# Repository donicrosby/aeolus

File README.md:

# Aeolus
A modular window extraction fan that uses common PC fans as the extraction component

## Setup
There are a few submodules that need to be pulled in this can be done by:

```bash
git clone --recurse-submodules https://github.com/donicrosby/aeolus.git
```

Or after already cloning the repo:

```bash
git clone ttps://github.com/donicrosby/aeolus.git
git submodule update --init --recursive
```

## Notes
This is a Kicad 9 project, ensure that you use that version when viewing

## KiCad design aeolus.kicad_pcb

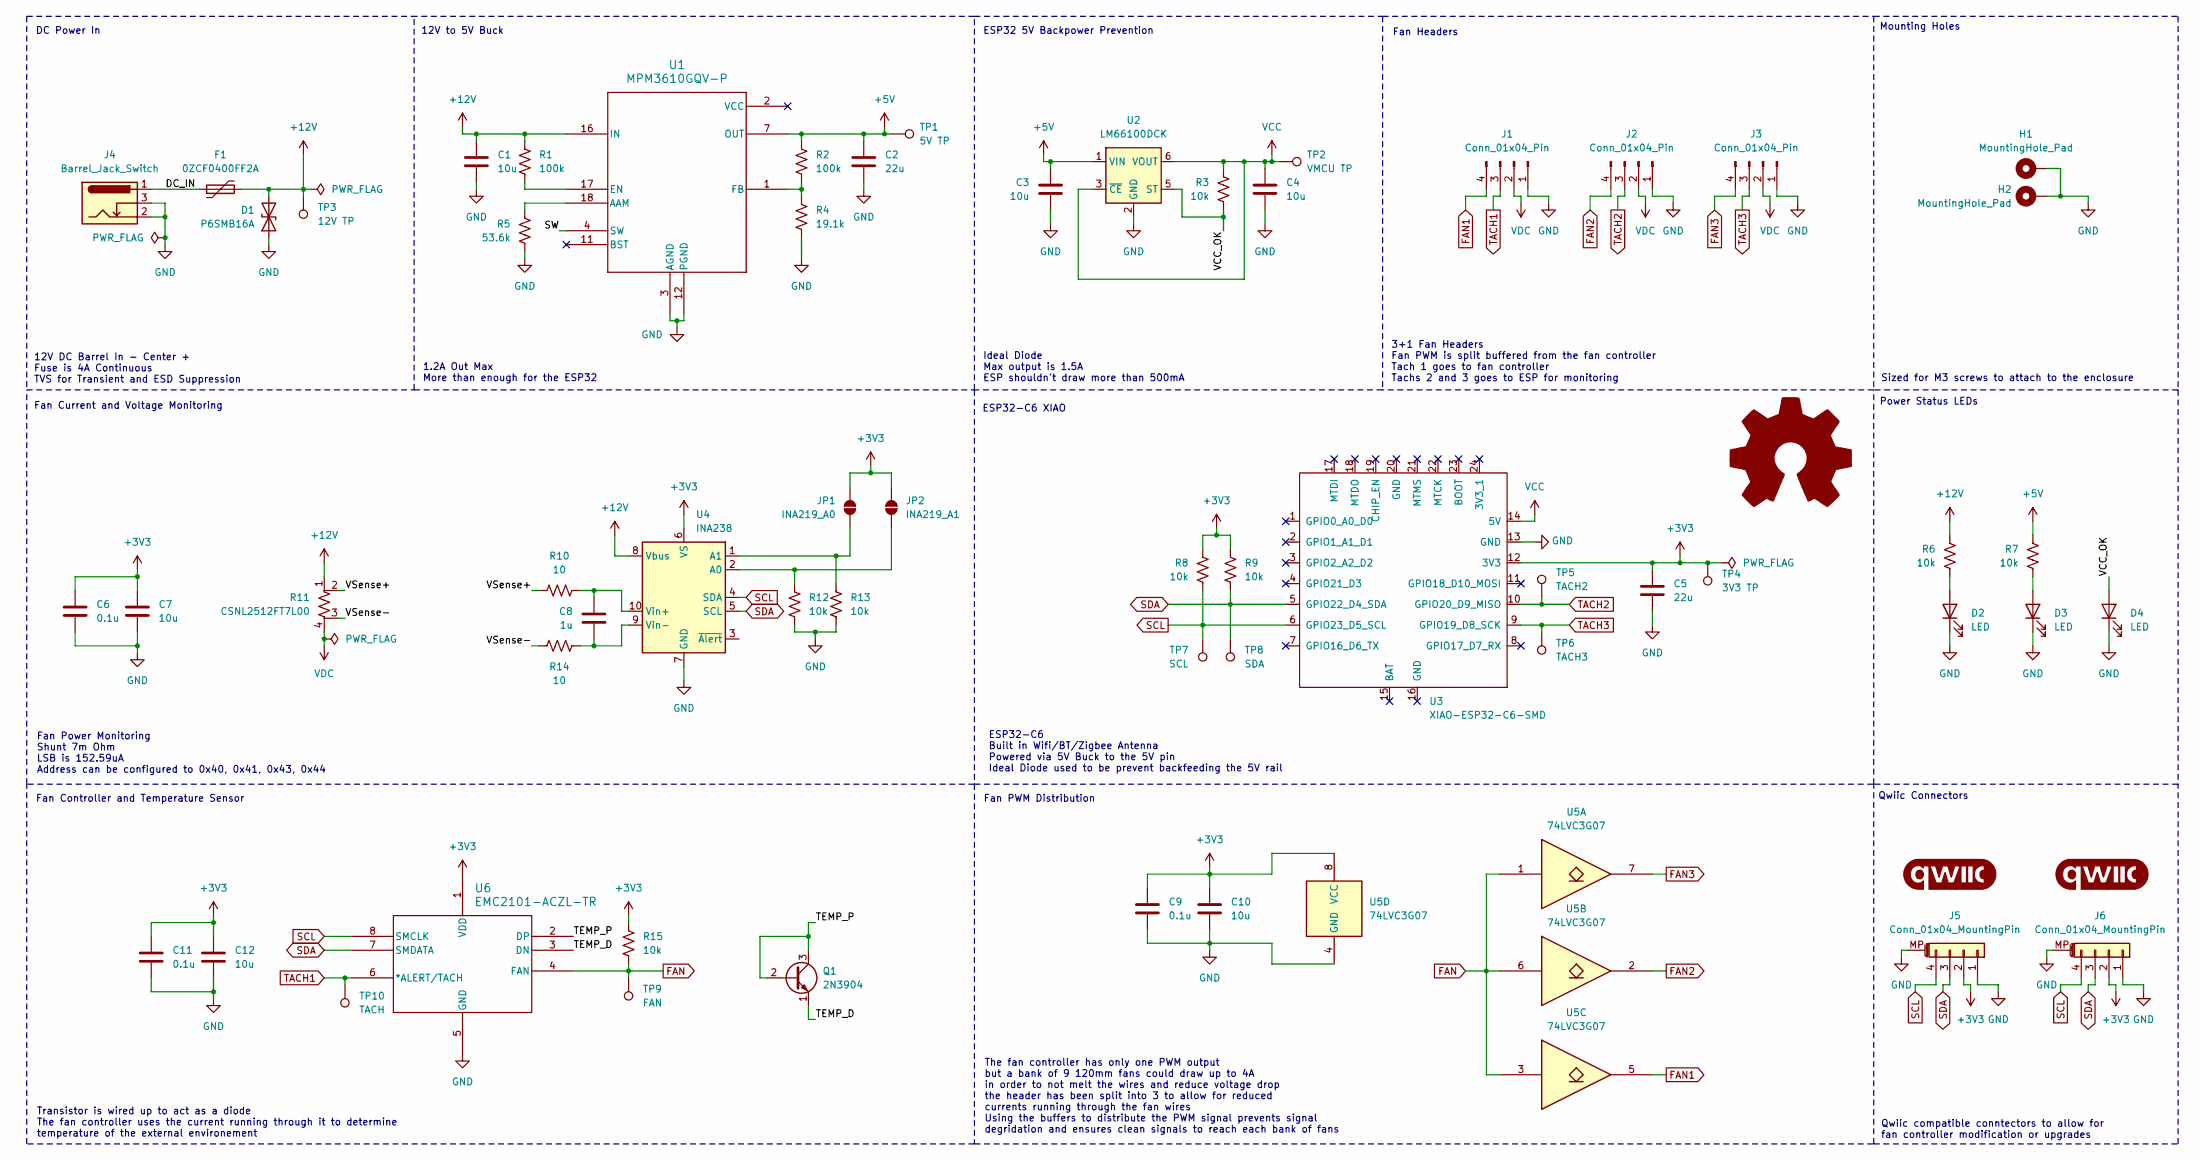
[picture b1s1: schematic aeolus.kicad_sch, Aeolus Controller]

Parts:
C1, C3, C4, C7, C10, C12: 10u; C_0805_2012Metric; MPN CL21A106KAYNNNE; LCSC C15850
C2, C5: 22u; C_0805_2012Metric; MPN CL21A226MAYNNNE; LCSC C602037
C6, C9, C11: 0.1u; C_0805_2012Metric; MPN CL21B104KBCNNNC; LCSC C5137467
C8: 1u; C_0805_2012Metric_Pad1.18x1.45mm_HandSolder; MPN CL21B105KBFNNNE; LCSC C5137467
D1: P6SMB16A; D_SMB; MPN P6SMB16A; LCSC C286252
D2: LED; LED_1206_3216Metric; MPN LTST-C150KSKT; LCSC C2985981
D3: LED; LED_1206_3216Metric; MPN LTST-C150KRKT; LCSC C2984265
D4: LED; LED_1206_3216Metric; MPN LTST-C150KGKT; LCSC C2984261
F1: 0ZCF0400FF2A; Fuse_2920_7451Metric; MPN 0ZCF0400FF2A
G1, G2: qwiic_Logo; qwiic_5.5mm
H1, H2: MountingHole_Pad; MountingHole_3.2mm_M3_Pad_Via
J1, J2, J3: Conn_01x04_Pin; FanPinHeader_1x04_P2.54mm_Vertical; MPN 470531000
J4: Barrel_Jack_Switch; BarrelJack_Wuerth_6941xx301002; MPN PJ-002AH
J5, J6: Conn_01x04_MountingPin; JST BM04B-SRSS-TB(LF)(SN)_4xP1.00mm; MPN BM04B-SRSS-TB(LF)(SN)
JP1: INA219_A0; SolderJumper-2_P1.3mm_Open_TrianglePad1.0x1.5mm
JP2: INA219_A1; SolderJumper-2_P1.3mm_Open_TrianglePad1.0x1.5mm
Q1: 2N3904; TO-92_Inline; MPN 2N3904
R1, R2: 100k; R_0805_2012Metric; MPN RC0805FR-07100KL; LCSC C96346
R3, R6, R7, R8, R9, R12, R13, R15: 10k; R_0805_2012Metric; MPN CRCW080510K0FKEAC; LCSC C84376
R4: 19.1k; R_0805_2012Metric; MPN RC0805FR-0719K1L; LCSC C2930175
R5: 53.6k; R_0805_2012Metric; MPN RC0805FR-0753K6L; LCSC C5153984
R10, R14: 10; R_0805_2012Metric_Pad1.20x1.40mm_HandSolder; MPN RM10J000CT; LCSC C17477
R11: CSNL2512FT7L00; Stackpole_Shunt_2512_Kelvin_7mOhm; MPN CMS-R050-1.0; LCSC C500733
TP1: 5V TP; TestPoint_Pad_D2.0mm
TP2: VMCU TP; TestPoint_Pad_D2.0mm
TP3: 12V TP; TestPoint_Pad_D2.0mm
TP4: 3V3 TP; TestPoint_Pad_D2.0mm
TP5: TACH2; TestPoint_Pad_D2.0mm
TP6: TACH3; TestPoint_Pad_D2.0mm
TP7: SCL; TestPoint_Pad_D2.0mm
TP8: SDA; TestPoint_Pad_D2.0mm
TP9: FAN; TestPoint_Pad_D2.0mm
TP10: TACH; TestPoint_Pad_D2.0mm
U1: MPM3610GQV-P; QFN3p0x5p0x1p6_MPM3610_MNP; MPN MPM3610GQV-P; LCSC C5183856
U2: LM66100DCK; SOT-363_SC-70-6; MPN LM66100DCKR; LCSC C2832141
U3: XIAO-ESP32-C6-SMD; XIAO-ESP32C6-SMD; MPN 113991254; LCSC C9900124963
U4: INA238; VSSOP-10_3x3mm_P0.5mm
U5: 74LVC3G07; SSOP-8_2.95x2.8mm_P0.65mm; MPN 74LVC3G07SS8-7; LCSC C2871847
U6: EMC2101-ACZL-TR; MSOP-8_3x3mm_P0.65mm; MPN EMC2101-ACZL-TR; LCSC C626967

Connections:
+3V3: C5.1, C6.1, C7.1, C9.1, C10.1, C11.1, C12.1, J5.2, J6.2, JP1.2 (B), JP2.2 (B), R8.1, R9.1, R15.1, TP4.1, U3.12 (3V3), U4.6 (VS), U5.8 (VCC), U6.1 (VDD)
+5V: C2.1, C3.1, R2.1, R7.1, TP1.1, U1.7 (OUT), U1.8 (OUT), U1.9 (OUT), U2.1 (VIN)
+12V: C1.1, D1.2 (A2), F1.2, R1.1, R6.1, R11.1, TP3.1, U1.16 (IN), U4.8 (Vbus)
/DC_IN: F1.1, J4.1
/SW: U1.4 (SW), U1.5 (SW), U1.6 (SW)
/TEMP_D: Q1.1 (E), U6.3 (DN)
/TEMP_P: Q1.2 (B), Q1.3 (C), U6.2 (DP)
/VCC_OK: D4.2 (A), R3.2, U2.5 (ST)
/VSense+: R10.1, R11.2
/VSense-: R11.3, R14.1
FAN: R15.2, TP9.1, U5.1, U5.3, U5.6, U6.4 (FAN)
FAN1: J1.4, U5.5
FAN2: J2.4, U5.2
FAN3: J3.4, U5.7
GND: C1.2, C2.2, C3.2, C4.2, C5.2, C6.2, C7.2, C9.2, C10.2, C11.2, C12.2, D1.1 (A1), D2.1 (K), D3.1 (K), D4.1 (K), H1.1, H2.1, J1.1, J2.1, J3.1, J4.2, J4.3, J5.1, J5.MP (MountPin), J6.1, J6.MP (MountPin), R4.2, R5.2, R12.2, R13.2, U1.3 (AGND), U1.12 (PGND), U1.13 (PGND), U1.14 (PGND), U2.2 (GND), U3.13 (GND), U4.7 (GND), U5.4 (GND), U6.5 (GND)
unnamed: D2.2 (A), R6.2
unnamed: D3.2 (A), R7.2
unnamed: JP1.1 (A), R13.1, U4.1 (A1)
unnamed: JP2.1 (A), R12.1, U4.2 (A0)
unnamed: R5.1, U1.18 (AAM)
unnamed: R1.2, U1.17 (EN)
unnamed: R2.2, R4.1, U1.1 (FB)
unnamed: C8.1, R10.2, U4.10 (Vin+)
unnamed: C8.2, R14.2, U4.9 (Vin-)
SCL: J5.4, J6.4, R8.2, TP7.1, U3.6 (GPIO23_D5_SCL), U4.4 (SDA), U6.8 (SMCLK)
SDA: J5.3, J6.3, R9.2, TP8.1, U3.5 (GPIO22_D4_SDA), U4.5 (SCL), U6.7 (SMDATA)
TACH1: J1.3, TP10.1, U6.6 (*ALERT/TACH)
TACH2: J2.3, TP5.1, U3.10 (GPIO20_D9_MISO)
TACH3: J3.3, TP6.1, U3.9 (GPIO19_D8_SCK)
VCC: C4.1, R3.1, TP2.1, U2.3 (~CE), U2.6 (VOUT), U3.14 (5V)
VDC: J1.2, J2.2, J3.2, R11.4

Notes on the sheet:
Fan Headers
Transistor is wired up to act as a diode The fan controller uses the current running through it to determine temperature of the external environement
ESP32 5V Backpower Prevention
12V to 5V Buck
3+1 Fan Headers Fan PWM is split buffered from the fan controller Tach 1 goes to fan controller Tachs 2 and 3 goes to ESP for monitoring
Ideal Diode Max output is 1.5A ESP shouldn't draw more than 500mA
Qwiic compatible conntectors to allow for fan controller modification or upgrades
The fan controller has only one PWM output but a bank of 9 120mm fans could draw up to 4A in order to not melt the wires and reduce voltage drop the header has been split into 3 to allow for reduced currents running through the fan wires Using the buffers to distribute the PWM signal prevents signa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
Fan Power Monitoring Shunt 7m Ohm LSB is 152.59uA Address can be configured to 0x40, 0x41, 0x43, 0x44
Mounting Holes
DC Power In
Sized for M3 screws to attach to the enclosure
1.2A Out Max More than enough for the ESP32
Fan Current and Voltage Monitoring
Fan PWM Distribution
12V DC Barrel In - Center + Fuse is 4A Continuous TVS for Transient and ESD Suppression
ESP32-C6 XIAO
Power Status LEDs
Fan Controller and Temperature Sensor
ESP32-C6 Built in Wifi/BT/Zigbee Antenna Powered via 5V Buck to the 5V pin Ideal Diode used to be prevent backfeeding the 5V rail
Qwiic Connectors

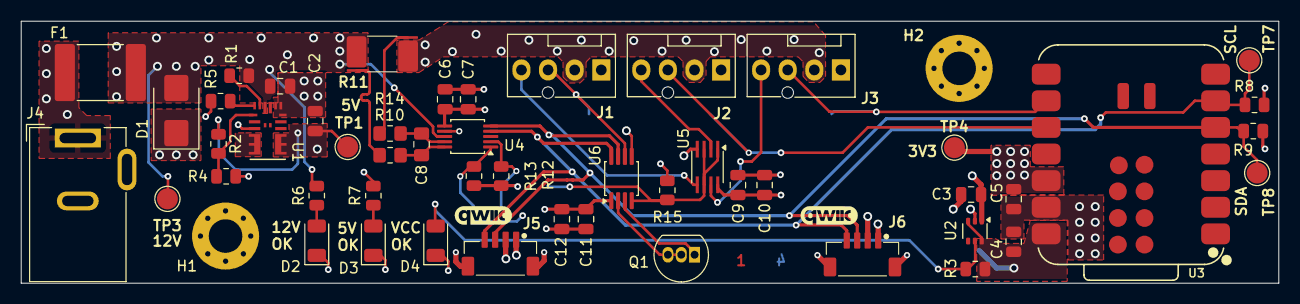
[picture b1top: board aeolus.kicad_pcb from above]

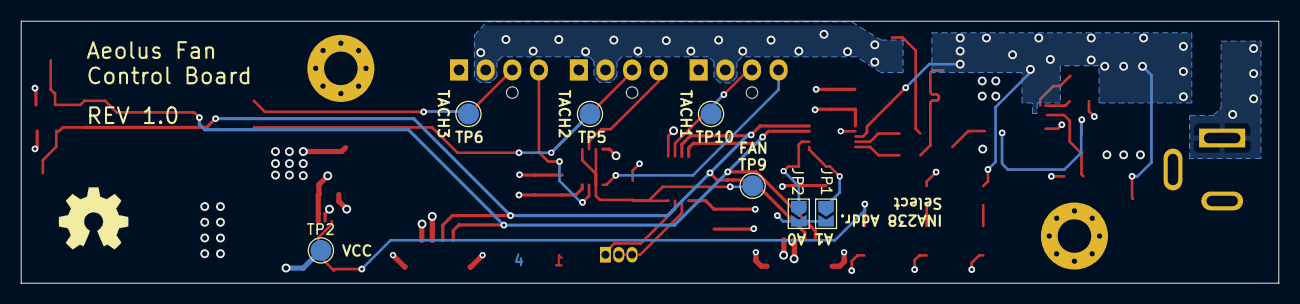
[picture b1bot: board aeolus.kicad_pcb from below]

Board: 4 copper layers, 120.0 x 25.0 mm, 61 parts (7 on the bottom side), 31 nets.

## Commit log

2025-12-01 feat: first pass at schematic
2025-12-01 More progress on PCB
2025-12-07 Inital pass at PCB
2025-12-08 Migrate to 4 layer board and beef up fan power distribution
2025-12-14 feat: update BOM for JLCPCB
2025-12-23 feat(bom): create production files
2025-12-24 fix(barrel jack): Fixed the fact that it was the wrong way around
2025-12-25 refactor: tweak design to be better for manufacturing
2025-12-28 refactor: use ina238 rather than ina219
2025-12-29 refactor: more tweaking of pcb
2025-12-29 feat: add qwiik connectors to board
2025-12-29 refactor: update Qwiic connector CAD model and footprint
2025-12-29 docs: update README
2025-12-29 style: added OSHW and Qwiic Logos to PCB and Schematic

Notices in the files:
aeolus.kicad_sch:
SPDX-License-Identifier: Apache-2.0 WITH SHL-2.1
